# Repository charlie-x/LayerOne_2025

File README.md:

# LayerOne 2025 GLiTCh BadgE

later on there are ai generated docs...

altium link.. there is an eror on one of the leds on the charlieplex'd leds...
also the 3 pin JST SWD is reversed
.
https://365.altium.com/files/01BF9671-6FB8-4A9E-9FD1-49A52BA8D165

first flash drive appears as RPI-RP2 copy the uf2 file to it, after that use the system command to reboot to the dfu or hold the RP-BOOT button during power on or a reset cycle

the pico-ice can be used to test the  fpga.

https://a360.co/4dxIxcs
terminal is CR, so do cr/lf conversion.

for 3v3 control the pads need to be soldered on the pcb,

switch_pwr  
short 1-2

glitch_ctrl
solder all three
short 1-2-3

3cv3_ctrl
short 1-2-3

fet
short 1-2-3

https://a360.co/4dxIxcs

thea re two pots vr1, vr2 , vr1 changes run votlage of vtg, vr2 controls the low voltage

diag scripts will find

Serial Ports for CMSIS-DAP
==========================

Found serial ports:
crw-rw-rw-  1 root  wheel  0x9000003 May 25 08:40 /dev/cu.usbmodem1202

first serial port is the CDC
crw-rw-rw-  1 root  wheel  0x9000005 May 25 08:40 /dev/cu.usbmodem14301

is for hook up to the fpga etc
crw-rw-rw-  1 root  wheel  0x9000009 May 25 08:40 /dev/cu.usbmodem14303

adc streaming , two adc's interlevaed see the adc python script

crw-rw-rw-  1 root  wheel  0x9000007 May 25 08:40 /dev/cu.usbmodem14305

the adc streaming is seperate and always runs

// run it
python adc_stream_reader.py /dev/cu.usbmodem14305

// pack ADC values into buffer
 - #define HEADER_BYTE 0xAA
 - #define PACKET_SIZE 5
 - 
 - void pack_adc_values(uint16_t _adc0, uint16_t _adc1, uint8_t seq, uint8_t* buffer) {
 -    buffer[0] = HEADER_BYTE;                      // header byte for synchronization
 -    buffer[1] = seq;                              // sequence number
 -     buffer[2] = _adc0 & 0xFF;                      // low 8 bits of adc0
 -     buffer[3] = ((_adc0 >> 8) & 0x0F) |            // high 4 bits of adc0
 -                 ((_adc1 & 0x0F) << 4);             // low 4 bits of adc1
 -     buffer[4] = (_adc1 >> 4) & 0xFF;               // high 8 bits of adc1
 - }

tats for LayerOne2025 codebase:

  Files by type:
  - C (.c): 57 files
  - Headers (.h): 48 files
  - Python (.py): 25 files
  - Markdown (.md): 17 files
  - Shell scripts (.sh): 8 files

  Code metrics:
  - Total lines of code: ~30,383 lines
  - Total commits: 82
  - Contributors: 2 (charliex: 82)

  Top directories:
  - Root directory (372 files)
  - cli/ (42 files)
  - docs/ (12 files)

## Overview

The LayerOne 2025 GLiTCh BadgE is a versatile hardware hacking platform designed for security researchers, hardware enthusiasts, and anyone interested in exploring digital electronics. It combines a powerful RP2040 microcontroller with specialized hardware for glitching, debugging, and interfacing with other devices.

## Features

- **RP2040 Microcontroller** - Dual-core ARM Cortex-M0+ processor
- **ICE40 FPGA** - Programmable logic for custom hardware implementations
- **Voltage Glitcher** - For performing precise voltage glitching attacks
- **Crowbar Circuit** - For power line manipulation
- **SWD Interface** - For debugging ARM-based targets
- **AVRISP** - For programming AVR microcontrollers
- **Analog Monitoring** - For capturing and analyzing signals
- **Multiple USB Modes** - Normal, DAP, and DFU modes for different use cases
- **Basic Logic Analyser** - Simple 12 bit LA at about 10khz
  
## Documentation

Comprehensive documentation is available in the [docs](docs/) directory:

- [Quick Start Guide](docs/quick_start.md) - Get up and running with your badge
- [CLI User Guide](docs/cli_user_guide.md) - Learn how to use the Command Line Interface
- [USB Modes Guide](docs/usb_modes_guide.md) - Understand the different USB modes
- [Hardware Hacking Guide](docs/hardware_hacking_guide.md) - Explore the hardware hacking features
- [Glitching Techniques Guide](docs/glitching_techniques.md) - Detailed guide on voltage, reset, and crowbar glitching
- [ADC Signal Analysis Guide](docs/adc_signal_analysis.md) - How to use the ADC for signal capture and analysis
- [AVRISP Programming Guide](docs/avrisp_programming_guide.md) - Program AVR microcontrollers with the badge
- [Documenting Research](docs/documenting_research.md) - Best practices for documenting hardware security research
- [Command Reference](docs/command_reference.md) - Quick reference for all CLI commands
- [Case Studies](docs/case_studies/README.md) - Real-world examples of hardware security vulnerabilities
  - [nRF52 Glitch Attack](docs/case_studies/nrf52_glitch_attack.md) - Voltage glitching attack on Nordic's BLE SoC

## Getting Started

### Prerequisites

- Python 3.6 or higher
- PySerial library (`pip install pyserial`)
- PyOCD for debugging (`pip install pyocd`)

### Installation

1. Clone this repository:
   ```
   git clone git@github.com:charlie-x/LayerOne_2025.git
   cd LayerOne_2025
   ```

2. Connect your badge to your computer using a USB-C cable
   Either use the RP-BOOT switch to put the badge into RPI-RP2 mode while its in reset, or switch on. or if its already flashed you can use system dfu command on the badge itself, copy the uf2/layerOne2025.uf2 file to the RPI-RP2 folder, use -X if you use cp in Mac OS
  
4. Run the CLI terminal:
   ```
   python3 cli_terminal.py
   ```

### Basic Usage

Once connected to the CLI, you can use commands like:

```
help            # Show available commands
status          # Show badge status
rgb on          # Turn on the RGB LED
usb mode dap    # Switch to DAP mode
```

For a complete list of commands, see the [Command Reference](docs/command_reference.md).

## USB Modes

The badge supports three USB modes:

1. **Normal Mode** (default) - 3 CDC interfaces + Mass Storage
2. **DAP Mode** - CMSIS-DAP debugging interface + CDC
3. **DFU Mode** - Device Firmware Update mode

To switch between modes, use the `usb mode` command:

```
usb mode normal     # Switch to normal mode
usb mode dap        # Switch to DAP mode
usb mode dfu        # Switch to DFU mode
```

## Logic Analyser mode

use command 

adc_stream la

## Development

### Building the Firmware

To build the firmware:

```
./build.sh
```

### Flashing the Firmware

To build and flash the firmware:

```
./build_and_flash.sh
```

### Running Tests

To run the USB mode tests:

```
python3 test_usb_modes.py
```

## Contributing

We welcome contributions to improve the badge and its documentation! Please see the [Contributing Guide](docs/contributing.md) for details on how to contribute.

## License

The LayerOne 2025 GLiTCh BadgE firmware and hardware designs are licensed under [MIT License](https://opensource.org/licenses/MIT).

## Acknowledgments

The LayerOne 2025 GLiTCh BadgE was created by NullSpaceLabs for the LayerOne 2025 conference. Special thanks to all the contributors and the hardware hacking community for their support and inspiration.

## Contact

- Website: [nullspacelabs.com](https://nullspacelabs.com)
- Email: [info@nullspacelabs.com](mailto:info@nullspacelabs.com)
- Twitter: [@nullspacelabs](https://twitter.com/nullspacelabs)

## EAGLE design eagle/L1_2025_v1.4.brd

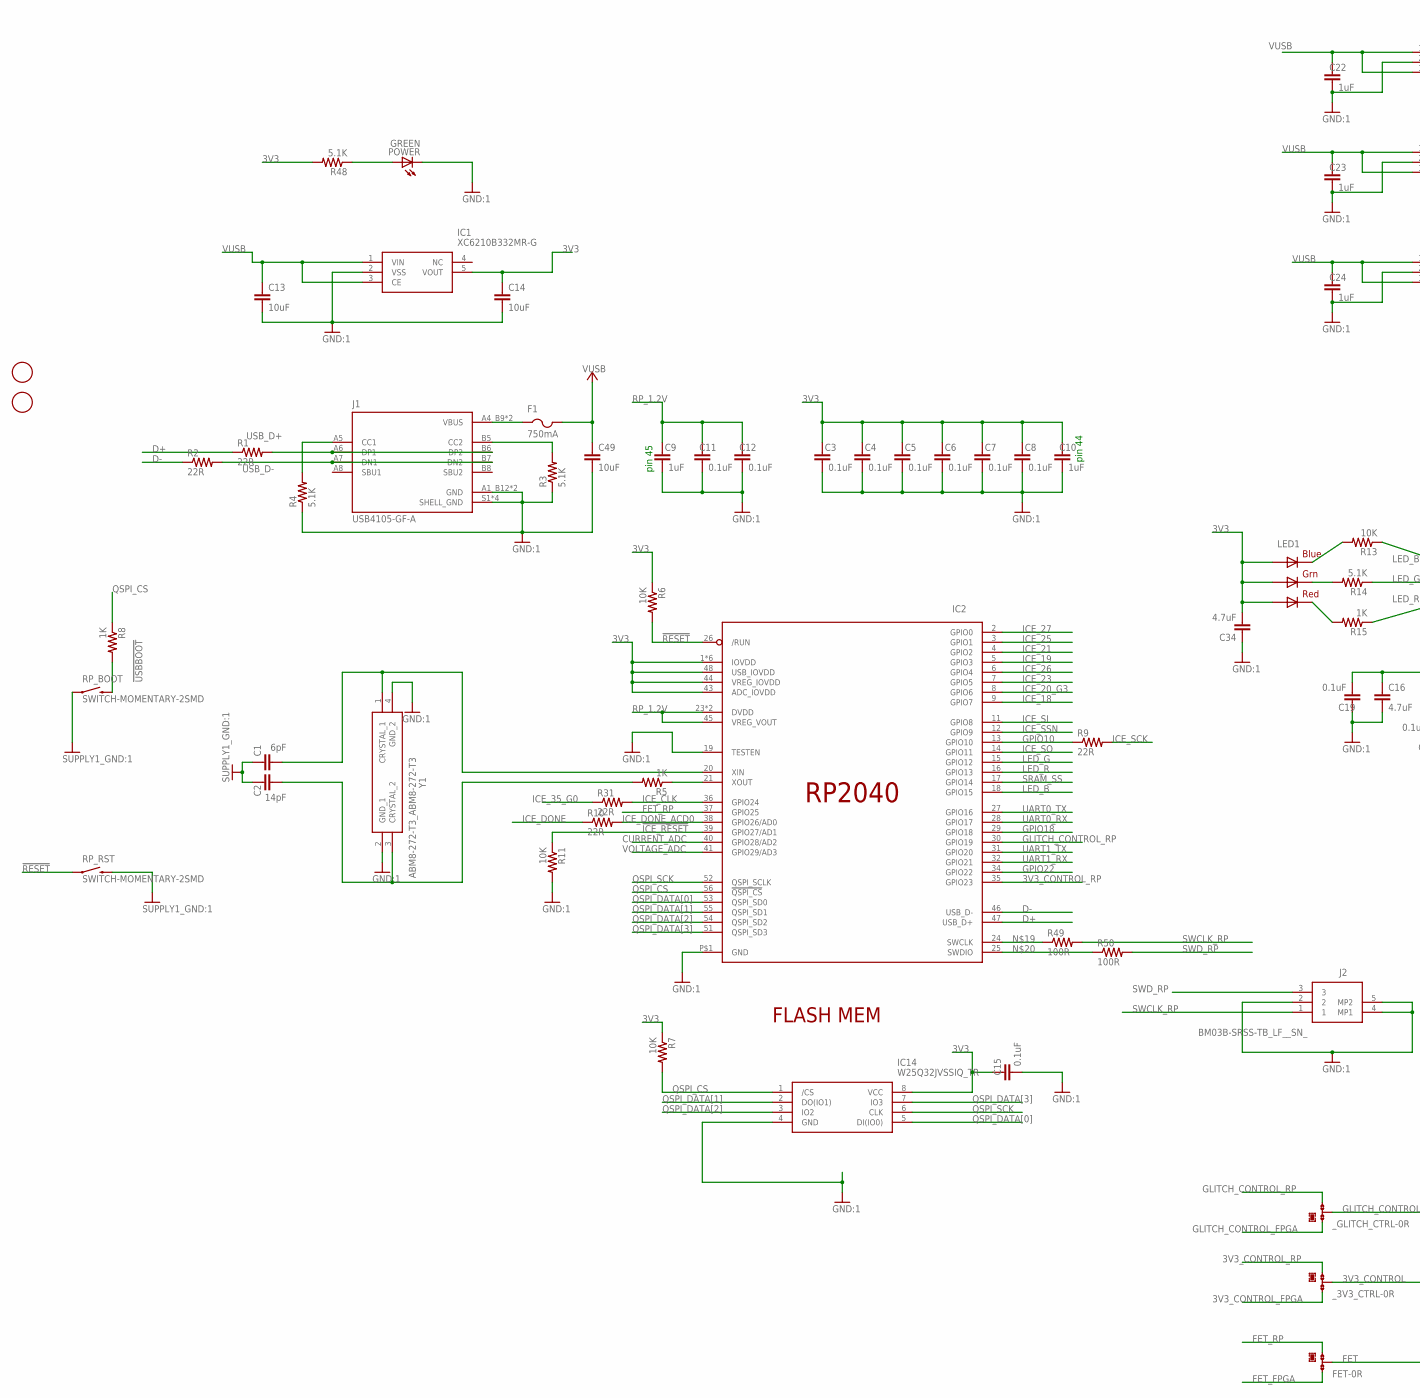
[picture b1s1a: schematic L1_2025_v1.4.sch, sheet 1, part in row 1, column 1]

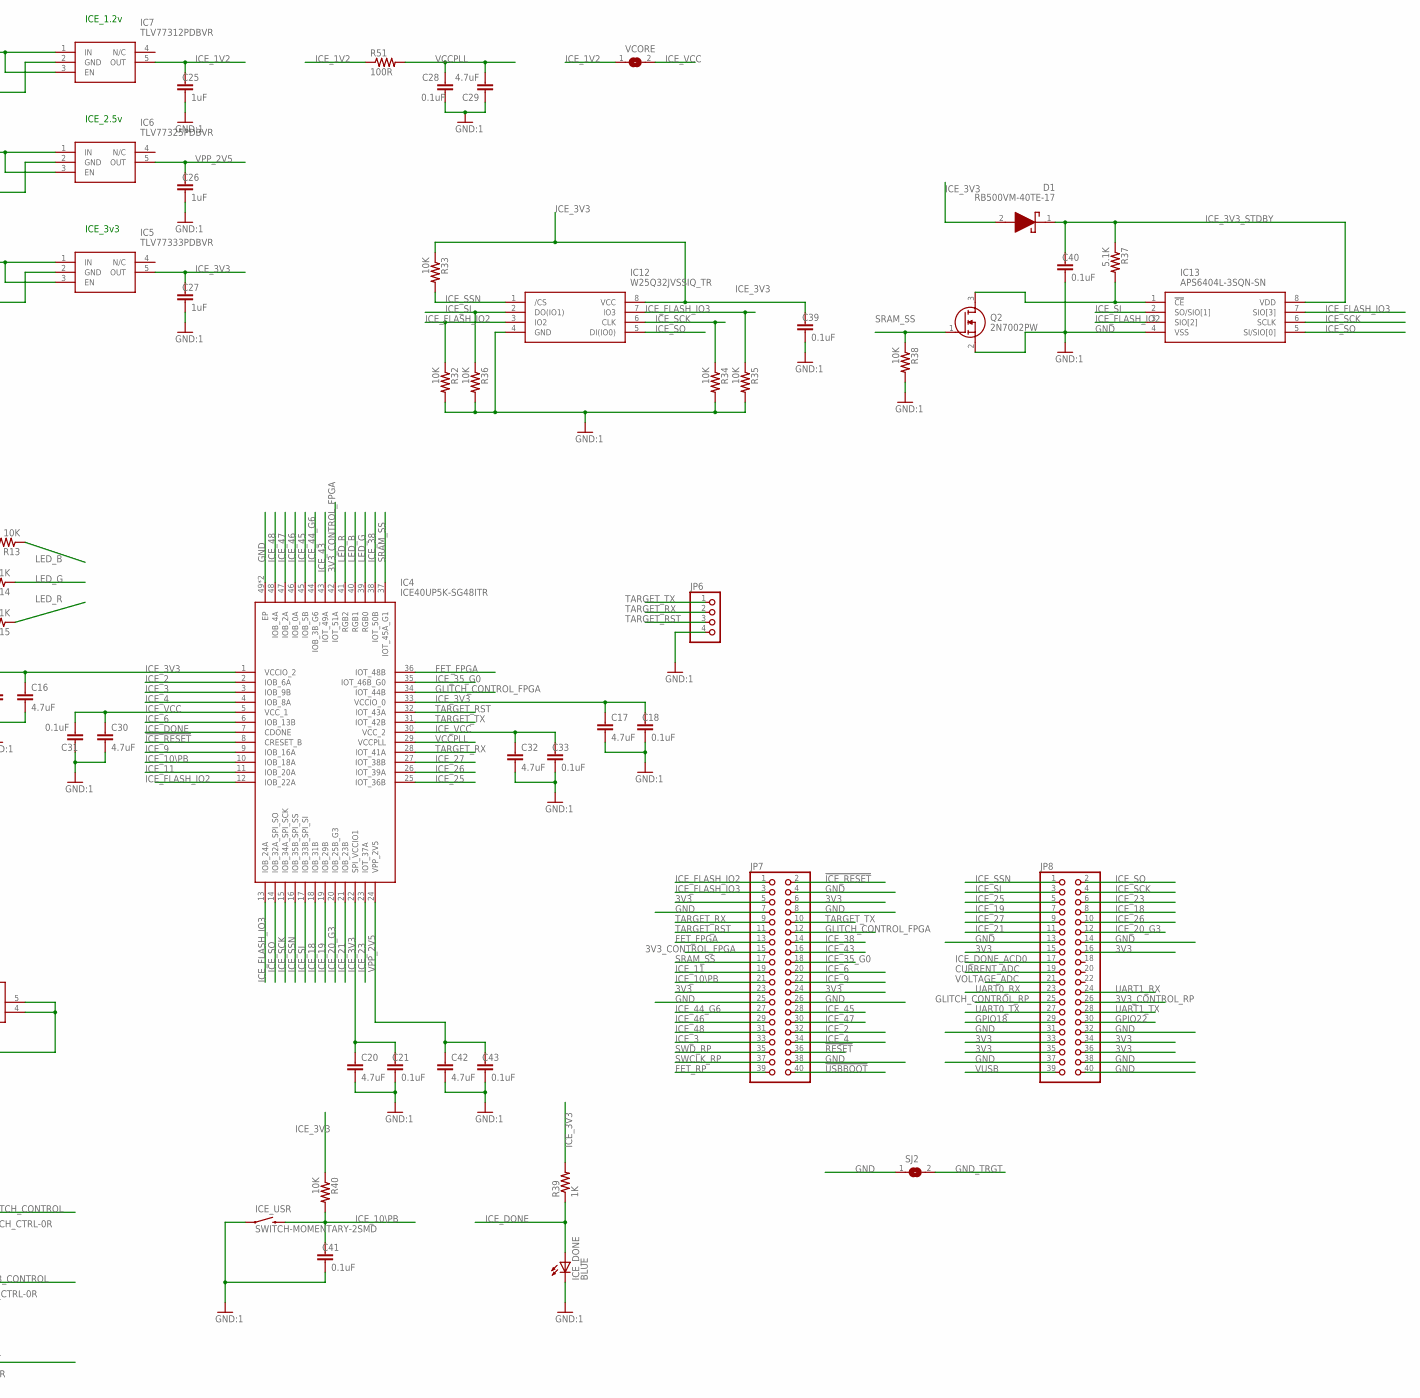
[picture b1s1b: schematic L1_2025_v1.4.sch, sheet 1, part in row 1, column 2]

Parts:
AFID1, AFID2: FIDUCIAL; FIDUCIAL_1MM
C1: 6pF; 0402-CAP
C2: 14pF; 0402-CAP
C3, C4, C5, C6, C7, C8, C11, C12, C15, C18, C19, C21, C28, C31, C33, C39, C40, C41, C43: 0.1uF; 0402-CAP
C9, C10, C22, C23, C24, C25, C26, C27: 1uF; 0402-CAP
C13, C14, C49: 10uF; 0603-CAP
C16, C17, C20, C29, C30, C32, C34, C42: 4.7uF; 0603-CAP
D1: RB500VM-40TE-17; RB500VM40TE17
F1: 750mA; R1206
FET: 0R-JUMPC; C0R-JMP
IC1: XC6210B332MR-G; SOT95P280X130-5N
IC2: ADAFRUIT_MICRO_RP2040_QFN56; ADAFRUIT_MICRO_QFN56_7MM_REDUCEDEPAD
IC4: ICE40UP5K-SG48ITR; QFN50P700X700X100-49N
IC5: TLV77333PDBVR; SOT95P280X145-5N
IC6: TLV77325PDBVR; SOT95P280X145-5N
IC7: TLV77312PDBVR; SOT95P280X145-5N
IC12, IC14: W25Q32JVSSIQ_TR; SOIC127P790X216-8N
IC13: APS6404L-3SQN-SN; SOIC127P600X175-8N
ICE_DONE: BLUE; LED-1206
ICE_USR: SWITCH-MOMENTARY-2SMD; TACTILE_SWITCH_SMD
J1: USB4105-GF-A; GCT_USB4105-GF-A
J2: BM03B-SRSS-TB_LF__SN_; BM03BSRSSTBLFSN
JP6: PINHD-1X4; 1X04
JP7, JP8: PINHD-2X20-BIG; 2X20-BIG
LED1: RGBLED5050
POWER: GREEN; LED-1206
Q2: 2N7002PW; SOT65P210X110-3N
R1, R2, R9, R10, R31: 22R; 0402-RES:1
R3, R4, R14, R37, R48: 5.1K; 0402-RES:1
R5, R8, R15, R39: 1K; 0402-RES:1
R6, R7, R11, R13, R32, R33, R34, R35, R36, R38, R40: 10K; 0402-RES:1
R49, R50, R51: 100R; 0402-RES:1
RP_BOOT: SWITCH-MOMENTARY-2SMD; TACTILE_SWITCH_SMD
RP_RST: SWITCH-MOMENTARY-2SMD; TACTILE_SWITCH_SMD
SJ2: SJ
VCORE: SJ
Y1: ABM8-272-T3_ABM8-272-T3; ABM8-272-T3_ABM8272T3
_3V3_CTRL: 0R-JUMPC; C0R-JMP
_GLITCH_CTRL: 0R-JUMPC; C0R-JMP

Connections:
3V3: C3.2, C4.2, C5.2, C6.2, C7.2, C8.2, C10.2, C14.1, C15.2, C34.2, IC1.5 (VOUT), IC2.1 (IOVDD), IC2.10 (IOVDD), IC2.22 (IOVDD), IC2.33 (IOVDD), IC2.42 (IOVDD), IC2.43 (ADC_IOVDD), IC2.44 (VREG_IOVDD), IC2.48 (USB_IOVDD), IC2.49 (IOVDD), IC14.8 (VCC), JP7.5, JP7.6, JP7.23, JP7.24, JP8.15, JP8.16, JP8.33, JP8.34, JP8.35, JP8.36, LED1.1 (GREEN_A), LED1.2 (RED_A), LED1.3 (BLUE_A), R6.1, R7.1, R48.2; also elsewhere on the board
3V3_CONTROL: _3V3_CTRL.2; also elsewhere on the board
3V3_CONTROL_FPGA: IC4.42 (IOT_51A), JP7.15, _3V3_CTRL.3
3V3_CONTROL_RP: IC2.35 (GPIO23), JP8.26, _3V3_CTRL.1
!ICE_RESET: IC2.39 (GPIO27/AD1), IC4.8 (CRESET_B), JP7.2, R11.1
!RESET: IC2.26 (/RUN), JP7.36, R6.2, RP_RST.1
!USBBOOT: JP7.40, R8.2, RP_BOOT.3 (2)
CURRENT_ADC: IC2.40 (GPIO28/AD2), JP8.19; also elsewhere on the board
D+: IC2.47 (USB_D+), R1.1
D-: IC2.46 (USB_D-), R2.1
FET: FET.2; also elsewhere on the board
FET_FPGA: FET.3, IC4.36 (IOT_48B), JP7.13
FET_RP: FET.1, IC2.37 (GPIO25), JP7.39
GLITCH_CONTROL: _GLITCH_CTRL.2; also elsewhere on the board
GLITCH_CONTROL_FPGA: IC4.34 (IOT_44B), JP7.12, _GLITCH_CTRL.3
GLITCH_CONTROL_RP: IC2.30 (GPIO19), JP8.25, _GLITCH_CTRL.1
GND: C1.1, C2.1, C3.1, C4.1, C5.1, C6.1, C7.1, C8.1, C9.1, C10.1, C11.1, C12.1, C13.2, C14.2, C15.1, C16.2, C17.2, C18.1, C19.2, C20.2, C21.1, C22.1, C23.1, C24.1, C25.1, C26.1, C27.1, C28.1, C29.1, C30.2, C31.2, C32.2, C33.1, C34.1, C39.1, C40.1, C41.1, C42.2, C43.1, C49.2, IC1.2 (VSS), IC2.19 (TESTEN), IC2.P$1 (GND), IC4.49 (EP), IC4.P$1 (EP), IC5.2 (GND), IC6.2 (GND), IC7.2 (GND), IC12.4 (GND), IC13.4 (VSS), IC14.4 (GND), ICE_DONE.C, ICE_USR.1, J1.A1_B12 (GND), J1.B1_A12 (GND), J1.S1 (SHELL_GND), J1.S2 (SHELL_GND), J1.S3 (SHELL_GND), J1.S4 (SHELL_GND), J2.2, J2.4 (MP1), J2.5 (MP2), JP6.4, JP7.4, JP7.7, JP7.8, JP7.25, JP7.26, JP7.38, JP8.13, JP8.14, JP8.31, JP8.32, JP8.37, JP8.38, JP8.40, POWER.C, Q2.2 (S), R3.1, R4.1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; also elsewhere on the board
GND_TRGT: SJ2.2; also elsewhere on the board
GPIO10: IC2.13 (GPIO10), R9.1
GPIO18: IC2.29 (GPIO18), JP8.29; also elsewhere on the board
GPIO22: IC2.34 (GPIO22), JP8.30; also elsewhere on the board
ICE_1V2: C25.2, IC7.5 (OUT), R51.1, VCORE.1
ICE_2: IC4.2 (IOB_6A), JP7.32
ICE_3: IC4.3 (IOB_9B), JP7.33
ICE_3V3: C16.1, C17.1, C18.2, C19.1, C20.1, C21.2, C27.2, C39.2, D1.2 (A), IC4.1 (VCCIO_2), IC4.22 (SPI_VCCIO1), IC4.33 (VCCIO_0), IC5.5 (OUT), IC12.8 (VCC), R33.1, R39.2, R40.1
ICE_3V3_STDBY: C40.2, D1.1 (K), IC13.8 (VDD), R37.1
ICE_4: IC4.4 (IOB_8A), JP7.34
ICE_6: IC4.6 (IOB_13B), JP7.20
ICE_9: IC4.9 (IOB_16A), JP7.22
ICE_10\PB: C41.2, IC4.10 (IOB_18A), ICE_USR.3 (2), JP7.21, R40.2
ICE_11: IC4.11 (IOB_20A), JP7.19
ICE_18: IC2.9 (GPIO7), IC4.18 (IOB_31B), JP8.8
ICE_19: IC2.5 (GPIO3), IC4.19 (IOB_29B), JP8.7
ICE_20_G3: IC2.8 (GPIO6), IC4.20 (IOB_25B_G3), JP8.12
ICE_21: IC2.4 (GPIO2), IC4.21 (IOB_23B), JP8.11
ICE_23: IC2.7 (GPIO5), IC4.23 (IOT_37A), JP8.6
ICE_25: IC2.3 (GPIO1), IC4.25 (IOT_36B), JP8.5
ICE_26: IC2.6 (GPIO4), IC4.26 (IOT_39A), JP8.10
ICE_27: IC2.2 (GPIO0), IC4.27 (IOT_38B), JP8.9
ICE_35_G0: IC4.35 (IOT_46B_G0), JP7.18, R31.1
ICE_38: IC4.38 (IOT_50B), JP7.14
ICE_43: IC4.43 (IOT_49A), JP7.16
ICE_44_G6: IC4.44 (IOB_3B_G6), JP7.27
ICE_45: IC4.45 (IOB_5B), JP7.28
ICE_46: IC4.46 (IOB_0A), JP7.29
ICE_47: IC4.47 (IOB_2A), JP7.30
ICE_48: IC4.48 (IOB_4A), JP7.31
ICE_CLK: IC2.36 (GPIO24), R31.2
ICE_DONE: IC4.7 (CDONE), ICE_DONE.A, R10.1, R39.1
ICE_DONE_ACD0: IC2.38 (GPIO26/AD0), JP8.17, R10.2
ICE_FLASH_IO2: IC4.12 (IOB_22A), IC12.3 (IO2), IC13.3 (SIO[2]), JP7.1, R32.1
ICE_FLASH_IO3: IC4.13 (IOB_24A), IC12.7 (IO3), IC13.7 (SIO[3]), JP7.3, R35.1
ICE_SCK: IC4.15 (IOB_34A_SPI_SCK), IC12.6 (CLK), IC13.6 (SCLK), JP8.4, R9.2, R34.1
ICE_SI: IC2.11 (GPIO8), IC4.17 (IOB_33B_SPI_SI), IC12.2 (DO(IO1)), IC13.2 (SO/SIO[1]), JP8.3, R36.1
ICE_SO: IC2.14 (GPIO11), IC4.14 (IOB_32A_SPI_SO), IC12.5 (DI(IO0)), IC13.5 (SI/SIO[0]), JP8.2
ICE_SSN: IC2.12 (GPIO9), IC4.16 (IOB_35B_SPI_SS), IC12.1 (/CS), JP8.1, R33.2
ICE_VCC: C30.1, C31.1, C32.1, C33.2, IC4.5 (VCC_1), IC4.30 (VCC_2), VCORE.2
LED_B: IC2.18 (GPIO15), IC4.40 (RGB1), R13.1
LED_G: IC2.15 (GPIO12), IC4.39 (RGB0), R14.1
LED_R: IC2.16 (GPIO13), IC4.41 (RGB2), R15.1
unnamed: C2.2, R5.2, Y1.3 (CRYSTAL_2)
unnamed: IC2.21 (XOUT), R5.1
unnamed: C1.2, IC2.20 (XIN), Y1.1 (CRYSTAL_1)
unnamed: LED1.4 (BLUE_C), R13.2
unnamed: LED1.6 (GREEN_C), R14.2
unnamed: LED1.5 (RED_C), R15.2
unnamed: J1.A5 (CC1), R4.2
unnamed: J1.B5 (CC2), R3.2
unnamed: IC13.1 (!CE), Q2.3 (D), R37.2
unnamed: F1.1, J1.A4_B9 (VBUS), J1.B4_A9 (VBUS)
unnamed: POWER.A, R48.1
unnamed: IC2.24 (SWCLK), R49.1
unnamed: IC2.25 (SWDIO), R50.1
QSPI_CS: IC2.56 (!QSPI_CS), IC14.1 (/CS), R7.2, R8.1
QSPI_DATA[0]: IC2.53 (QSPI_SD0), IC14.5 (DI(IO0))
QSPI_DATA[1]: IC2.55 (QSPI_SD1), IC14.2 (DO(IO1))
QSPI_DATA[2]: IC2.54 (QSPI_SD2), IC14.3 (IO2)
QSPI_DATA[3]: IC2.51 (QSPI_SD3), IC14.7 (IO3)
QSPI_SCK: IC2.52 (QSPI_SCLK), IC14.6 (CLK)
RP_1.2V: C9.2, C11.2, C12.2, IC2.23 (DVDD), IC2.45 (VREG_VOUT), IC2.50 (DVDD)
SRAM_SS: IC2.17 (GPIO14), IC4.37 (IOT_45A_G1), JP7.17, Q2.1 (G), R38.1
SWCLK_RP: J2.1, JP7.37, R49.2
SWD_RP: J2.3, JP7.35, R50.2
TARGET_RST: IC4.32 (IOT_43A), JP6.3, JP7.11
TARGET_RX: IC4.28 (IOT_41A), JP6.2, JP7.9
TARGET_TX: IC4.31 (IOT_42B), JP6.1, JP7.10
UART0_RX: IC2.28 (GPIO17), JP8.23; also elsewhere on the board
UART0_TX: IC2.27 (GPIO16), JP8.27; also elsewhere on the board
UART1_RX: IC2.32 (GPIO21), JP8.24; also elsewhere on the board
UART1_TX: IC2.31 (GPIO20), JP8.28; also elsewhere on the board
USB_D+: J1.A6 (DP1), J1.B6 (DP2), R1.2
USB_D-: J1.A7 (DN1), J1.B7 (DN2), R2.2
VCCPLL: C28.2, C29.2, IC4.29 (VCCPLL), R51.2
VOLTAGE_ADC: IC2.41 (GPIO29/AD3), JP8.21; also elsewhere on the board
VPP_2V5: C26.2, C42.1, C43.2, IC4.24 (VPP_2V5), IC6.5 (OUT)
VUSB: C13.1, C22.2, C23.2, C24.2, C49.1, F1.2, IC1.1 (VIN), IC1.3 (CE), IC5.1 (IN), IC5.3 (EN), IC6.1 (IN), IC6.3 (EN), IC7.1 (IN), IC7.3 (EN), JP8.39; also elsewhere on the board

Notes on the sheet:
pin 45
pin 44
FLASH MEM
ICE_3v3
ICE_2.5v
ICE_1.2v

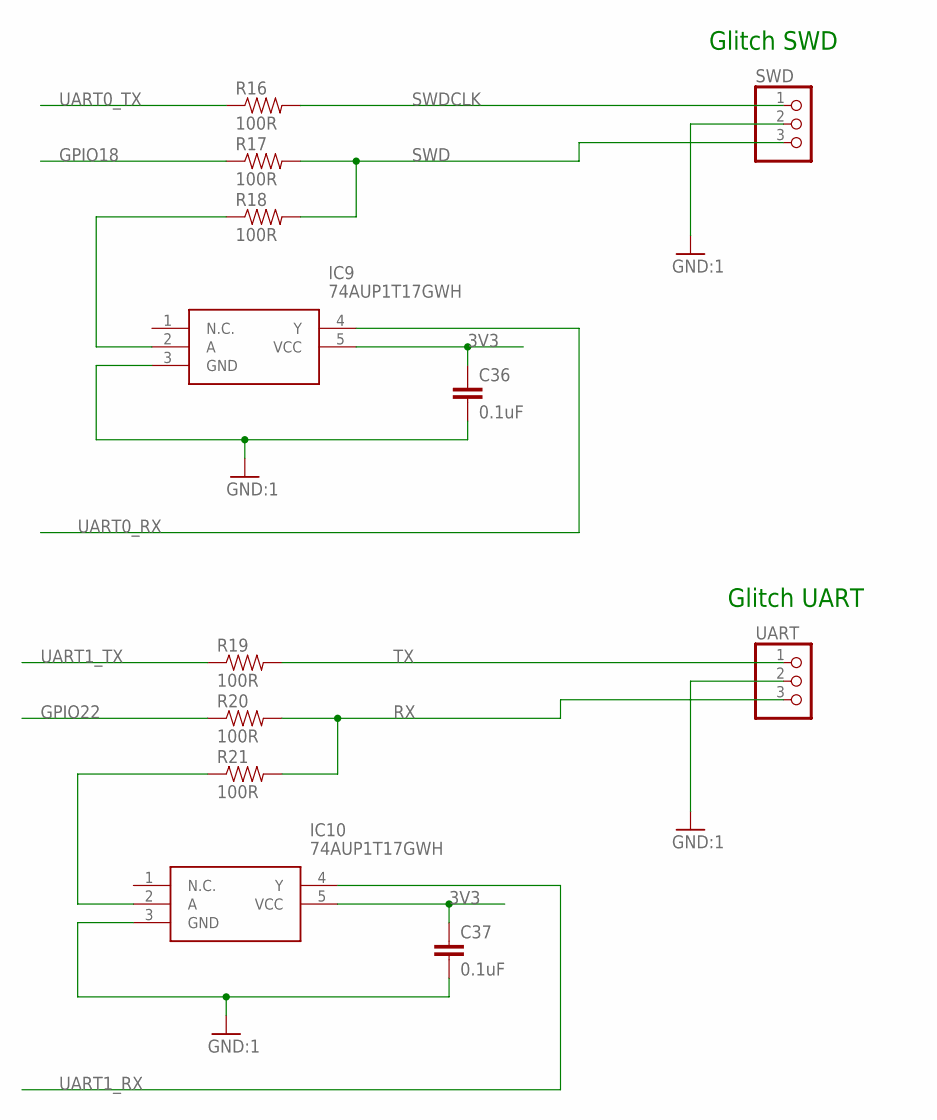
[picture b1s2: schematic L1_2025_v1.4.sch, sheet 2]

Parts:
C36, C37: 0.1uF; 0402-CAP
IC9, IC10: 74AUP1T17GWH; SOT65P212X110-5N
R16, R17, R18, R19, R20, R21: 100R; 0402-RES:1
SWD: PINHD-1X3; 1X03
UART: PINHD-1X3; 1X03

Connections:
3V3: C36.1, C37.1, IC9.5 (VCC), IC10.5 (VCC); also elsewhere on the board
GND: C36.2, C37.2, IC9.3 (GND), IC10.3 (GND), SWD.2, UART.2; also elsewhere on the board
GPIO18: R17.1; also elsewhere on the board
GPIO22: R20.1; also elsewhere on the board
unnamed: IC10.2 (A), R21.1
unnamed: IC9.2 (A), R18.1
RX: R20.2, R21.2, UART.3
SWD: R17.2, R18.2, SWD.3
SWDCLK: R16.2, SWD.1
TX: R19.2, UART.1
UART0_RX: IC9.4 (Y); also elsewhere on the board
UART0_TX: R16.1; also elsewhere on the board
UART1_RX: IC10.4 (Y); also elsewhere on the board
UART1_TX: R19.1; also elsewhere on the board

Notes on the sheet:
Glitch SWD
Glitch UART

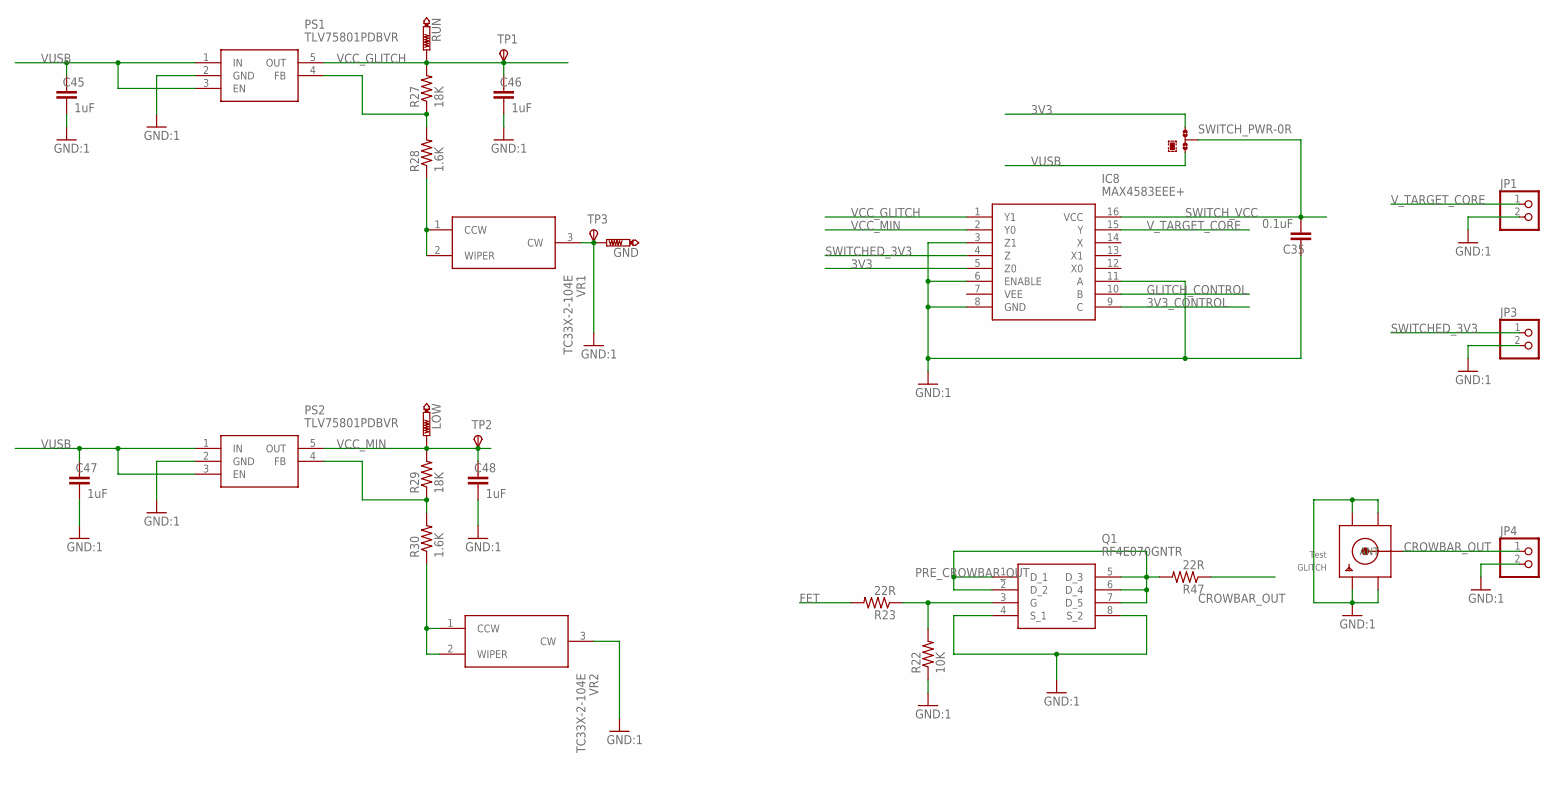
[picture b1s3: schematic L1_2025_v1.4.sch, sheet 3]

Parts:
C35: 0.1uF; 0402-CAP
C45, C46, C47, C48: 1uF; 0402-CAP
GLITCH: Test; SMA_EDGELAUNCH
GND: PTR1PAD1-13; P1-13
IC8: MAX4583EEE+; SOP64P602X175-16N
JP1, JP3, JP4: PINHD-1X2; 1X02
LOW: PTR1PAD1-13; P1-13
PS1, PS2: TLV75801PDBVR; SOT95P280X145-5N
Q1: RF4E070GNTR
R22: 10K; 0402-RES:1
R23, R47: 22R; 0402-RES:1
R27, R29: 18K; 0402-RES:1
R28, R30: 1.6K; 0402-RES:1
RUN: PTR1PAD1-13; P1-13
SWITCH_PWR: 0R-JUMPC; C0R-JMP
TP1, TP2, TP3: TESTPAD_TPSTP20R; TESTPAD_TP20R:1
VR1, VR2: TC33X-2-104E; TC33X2503E

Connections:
3V3: IC8.5 (Z0), SWITCH_PWR.1; also elsewhere on the board
3V3_CONTROL: IC8.9 (C); also elsewhere on the board
CROWBAR_OUT: GLITCH.P (ANT), JP4.1, R47.1
FET: R23.2; also elsewhere on the board
GLITCH_CONTROL: IC8.10 (B); also elsewhere on the board
GND: C35.2, C45.1, C46.1, C47.1, C48.1, GLITCH.GND@1 (GND4), GLITCH.GND@2 (GND3), GLITCH.GND@3 (GND2), GLITCH.GND@4 (GND1), GND.TP, IC8.3 (Z1), IC8.6 (ENABLE), IC8.8 (GND), IC8.11 (A), JP1.2, JP3.2, JP4.2, PS1.2 (GND), PS2.2 (GND), Q1.4 (S_1), Q1.8 (S_2), R22.1, TP3.TP, VR1.3 (CW), VR2.3 (CW); also elsewhere on the board
unnamed: PS1.4 (FB), R27.1, R28.2
unnamed: Q1.3 (G), R22.2, R23.1
unnamed: R28.1, VR1.1 (CCW), VR1.2 (WIPER)
unnamed: PS2.4 (FB), R29.1, R30.2
unnamed: R30.1, VR2.1 (CCW), VR2.2 (WIPER)
PRE_CROWBAR_OUT: Q1.1 (D_1), Q1.2 (D_2), Q1.5 (D_3), Q1.6 (D_4), Q1.7 (D_5), R47.2
SWITCHED_3V3: IC8.4 (Z), JP3.1
SWITCH_VCC: C35.1, IC8.16 (VCC), SWITCH_PWR.2
VCC_GLITCH: C46.2, IC8.1 (Y1), PS1.5 (OUT), R27.2, RUN.TP, TP1.TP
VCC_MIN: C48.2, IC8.2 (Y0), LOW.TP, PS2.5 (OUT), R29.2, TP2.TP
VUSB: C45.2, C47.2, PS1.1 (IN), PS1.3 (EN), PS2.1 (IN), PS2.3 (EN), SWITCH_PWR.3; also elsewhere on the board
V_TARGET_CORE: IC8.15 (Y), JP1.1

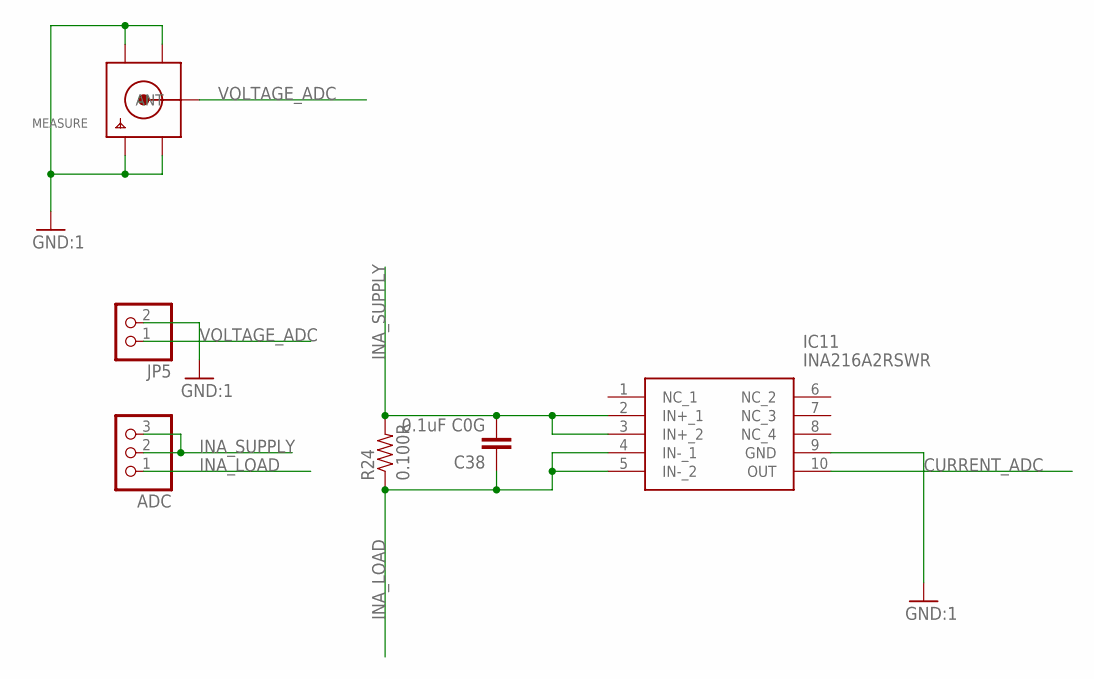
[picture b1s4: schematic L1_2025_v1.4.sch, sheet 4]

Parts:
ADC: PINHD-1X3:1; 1X03:1
C38: 0.1uF C0G; 0402-CAP
IC11: INA216A2RSWR
JP5: PINHD-1X2; 1X02
MEASURE: SMACONNECTOR_EDGE; SMA_EDGELAUNCH
R24: 0.100R; R2512

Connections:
CURRENT_ADC: IC11.10 (OUT); also elsewhere on the board
GND: IC11.9 (GND), JP5.2, MEASURE.GND@1 (GND4), MEASURE.GND@2 (GND3), MEASURE.GND@3 (GND2), MEASURE.GND@4 (GND1); also elsewhere on the board
INA_LOAD: ADC.1, C38.1, IC11.4 (IN-_1), IC11.5 (IN-_2), R24.1
INA_SUPPLY: ADC.2, ADC.3, C38.2, IC11.2 (IN+_1), IC11.3 (IN+_2), R24.2
VOLTAGE_ADC: JP5.1, MEASURE.P (ANT); also elsewhere on the board

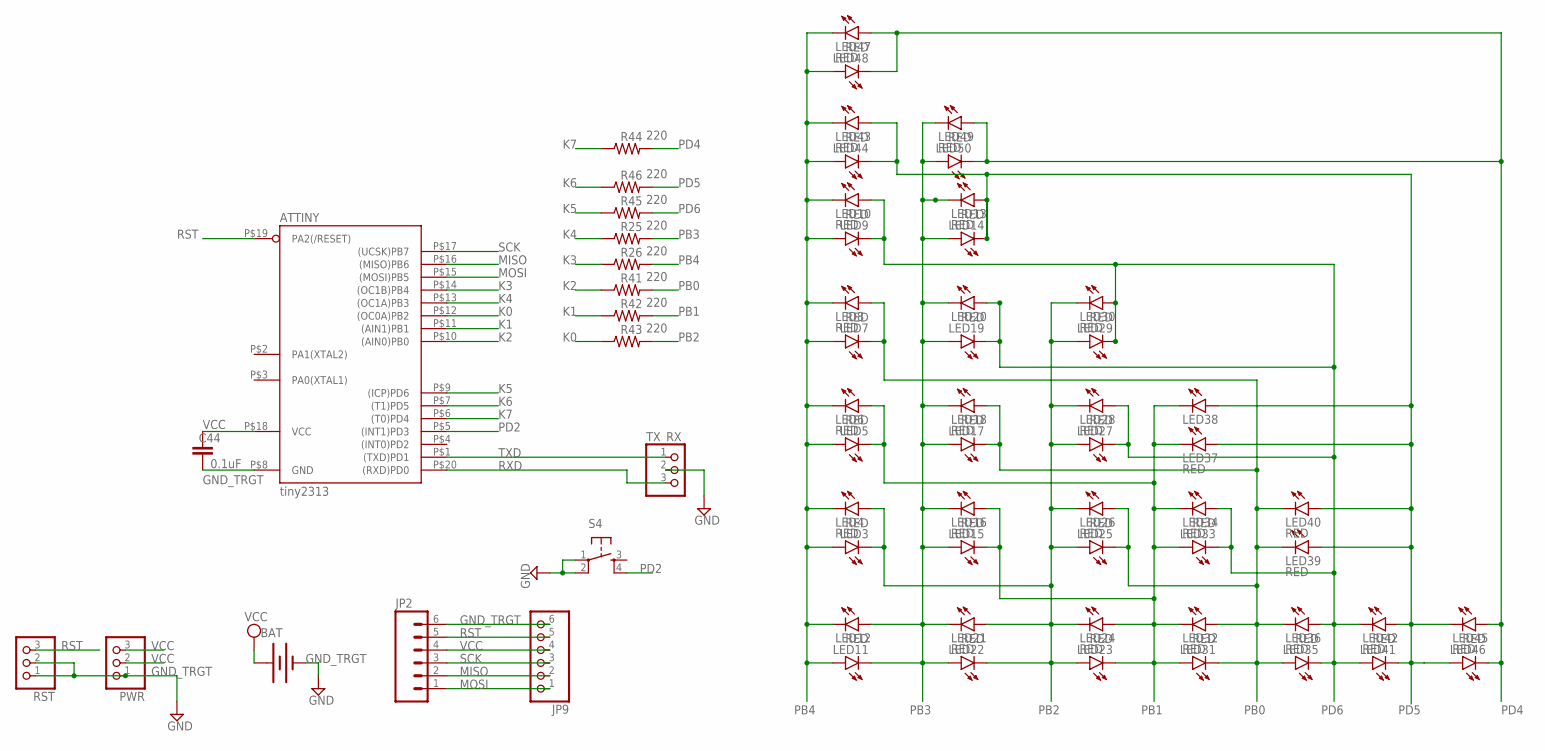
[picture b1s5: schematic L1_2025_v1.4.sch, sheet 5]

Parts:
ATTINY: tiny2313; MLF20
BAT: SPARKFUN_BATTERYSPARKFUN_BATTCOMM_20MM_LINX; SPARKFUN_BATTCOM_20MM_LINX
C44: 0.1uF; 0402-CAP
JP2: SPARKFUN-CONNECTORS_M06SMD-FEMALE-V2; SPARKFUN-CONNECTORS_1X06-SMD-FEMALE-V2
JP9: ADAFRUIT_PINHD-1X6CLEAN; ADAFRUIT_1X06-CLEAN
LED3, LED4, LED5, LED6, LED7, LED8, LED9, LED10, LED11, LED13, LED14, LED15, LED16, LED17, LED18, LED19, LED21, LED22, LED23, LED24, LED25, LED26, LED27, LED28, LED29, LED30, LED31, LED32, LED33, LED34, LED35, LED36, LED37, LED39, LED40, LED41, LED42, LED43, LED44, LED45, LED46, LED47, LED48, LED49, LED50: RED; CHIPLED_1206
LED12, LED20, LED38: LEDCHIPLED_1206:1; CHIPLED_1206
PWR: PINHD-1X3; 1X03
R25, R26, R41, R42, R43, R44, R45, R46: 220; 0805
RST: PINHD-1X3; 1X03
S4: TAC_SWITCHSMD; TACTILE_SWITCH_SMD:1
TX_RX: PINHD-1X3; 1X03

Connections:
GND_TRGT: ATTINY.P$8 (GND), BAT.2 (-), C44.1, JP2.6, JP9.6, PWR.1, RST.1, RST.2, S4.1, S4.2, TX_RX.2; also elsewhere on the board
K0: ATTINY.P$12 ((OC0A)PB2), R43.1
K1: ATTINY.P$11 ((AIN1)PB1), R42.1
K2: ATTINY.P$10 ((AIN0)PB0), R41.1
K3: ATTINY.P$14 ((OC1B)PB4), R26.1
K4: ATTINY.P$13 ((OC1A)PB3), R25.1
K5: ATTINY.P$9 ((ICP)PD6), R45.1
K6: ATTINY.P$7 ((T1)PD5), R46.1
K7: ATTINY.P$6 ((T0)PD4), R44.1
MISO: ATTINY.P$16 ((MISO)PB6), JP2.2, JP9.2
MOSI: ATTINY.P$15 ((MOSI)PB5), JP2.1, JP9.1
PB0: LED7.C, LED8.A, LED17.C, LED18.A, LED25.C, LED26.A, LED31.C, LED32.A, LED35.A, LED36.C, LED39.C, LED40.C, R41.2
PB1: LED5.C, LED6.A, LED15.C, LED16.A, LED23.C, LED24.A, LED31.A, LED32.C, LED33.A, LED34.C, LED37.C, LED38.C, R42.2
PB2: LED3.C, LED4.A, LED21.A, LED22.C, LED23.A, LED24.C, LED25.A, LED26.C, LED27.A, LED28.C, LED29.A, LED30.C, R43.2
PB3: LED11.C, LED12.A, LED13.C, LED14.A, LED15.A, LED16.C, LED17.A, LED18.C, LED19.A, LED20.C, LED21.C, LED22.A, LED49.C, LED50.A, R25.2
PB4: LED3.A, LED4.C, LED5.A, LED6.C, LED7.A, LED8.C, LED9.A, LED10.C, LED11.A, LED12.C, LED43.C, LED44.A, LED47.C, LED48.A, R26.2
PD2: ATTINY.P$5 ((INT1)PD3), S4.4
PD4: LED45.A, LED46.C, LED47.A, LED48.C, LED49.A, LED50.C, R44.2
PD5: LED13.A, LED14.C, LED37.A, LED38.A, LED39.A, LED40.A, LED41.C, LED42.A, LED43.A, LED44.C, LED45.C, LED46.A, R46.2
PD6: LED9.C, LED10.A, LED19.C, LED20.A, LED27.C, LED28.A, LED29.C, LED30.A, LED33.C, LED34.A, LED35.C, LED36.A, LED41.A, LED42.C, R45.2
RST: ATTINY.P$19 (PA2(/RESET)), JP2.5, JP9.5, RST.3
RXD: ATTINY.P$20 ((RXD)PD0), TX_RX.3
SCK: ATTINY.P$17 ((UCSK)PB7), JP2.3, JP9.3
TXD: ATTINY.P$1 ((TXD)PD1), TX_RX.1
VCC: ATTINY.P$18 (VCC), BAT.1 (+), C44.2, JP2.4, JP9.4, PWR.2, PWR.3

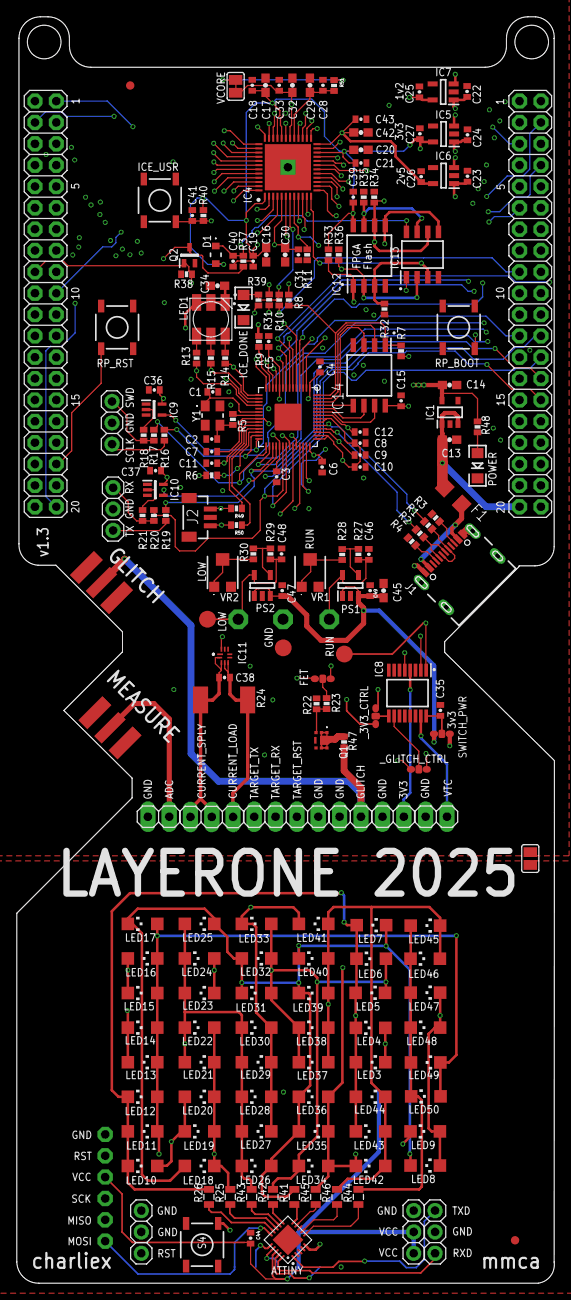
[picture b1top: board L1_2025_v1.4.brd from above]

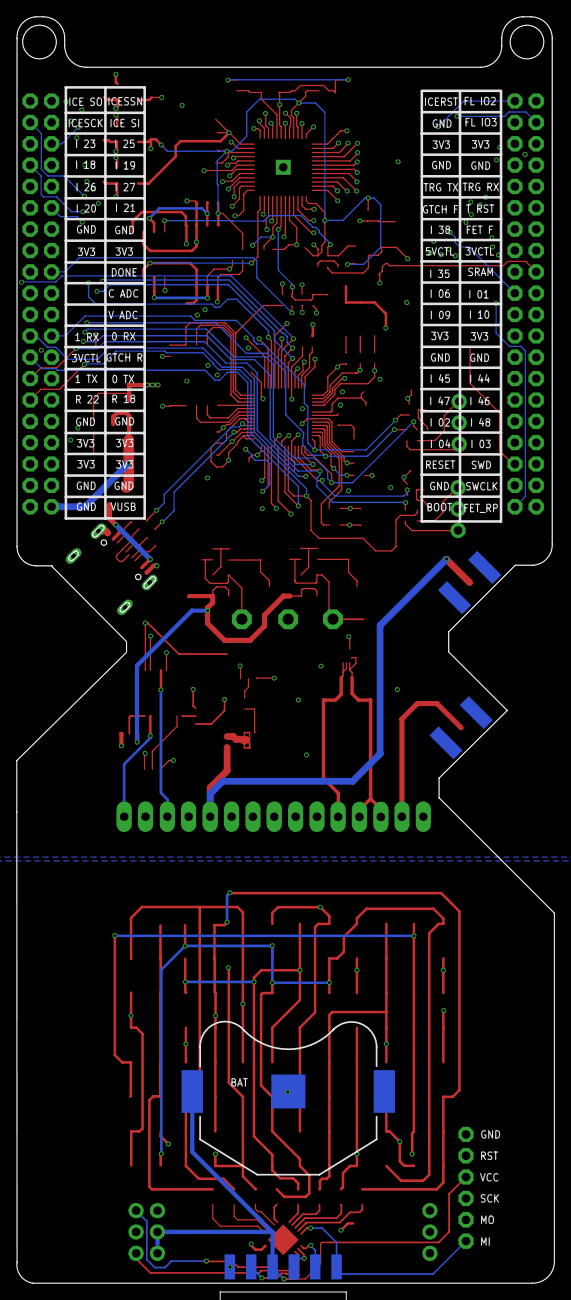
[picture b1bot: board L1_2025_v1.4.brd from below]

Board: 4 copper layers, 64.0 x 150.7 mm, 211 parts (2 on the bottom side), 140 nets.

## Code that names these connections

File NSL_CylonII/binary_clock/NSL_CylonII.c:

#include <avr/io.h> 
#include <avr/eeprom.h> 
#include <avr/interrupt.h>
#include <avr/pgmspace.h>

#include <util/delay.h>

#include <stdlib.h>

#define shortdelay(); 			asm("nop\n\tnop\n\t");

#define TIMER1_PRESCALE_1 		(1)
#define TIMER1_PRESCALE_8 		(2)
#define TIMER1_PRESCALE_64 		(3)
#define TIMER1_PRESCALE_256		(4)
#define TIMER1_PRESCALE_1024	(5)

#define MIN_OF(x,y) ((x) < (y) ? (x) : (y))
#define MAX_OF(x,y) ((x) > (y) ? (x) : (y))

#define GET_BIT(a,n)    ((a >> n) & 1)
#define SET_BIT(a,n)    (a|=(1<<n))
#define CLR_BIT(a,n)    (a&=~(1<<n))
#define SWITCH_BIT(a,n) (a^=(1<<n))
#define IS_BIT_SET(a,n) (a & (1<<n))
#define IS_BIT_CLR(a,n) (~(a & (1<<n)))

// 		PORTB,DDRB,PINB

#define ddrb(r,c)  charlieplex[ (r*(3*4)) + ((c*3)+1) ]
#define pinb(r,c)  charlieplex[ (r*(3*4)) + ((c*3)+2) ]
#define portb(r,c) charlieplex[ (r*(3*4)) + ((c*3)+0) ]

#define HEX__(n) 0x##n##LU

/* 8-bit conversion function */
#define B8__(x) ((x&0x0000000FLU)?1:0)	\
	+((x&0x000000F0LU)?2:0)		\
	+((x&0x00000F00LU)?4:0)		\
	+((x&0x0000F000LU)?8:0)		\
	+((x&0x000F0000LU)?16:0)	\
	+((x&0x00F00000LU)?32:0)	\
	+((x&0x0F000000LU)?64:0)	\
	+((x&0xF0000000LU)?128:0)

/* *** user macros ***/

/* for upto 8-bit binary constants */
#define B8(d) ((unsigned char)B8__(HEX__(d)))

/* for upto 16-bit binary constants, MSB first */
#define B16(dmsb,dlsb) (((unsigned short)B8(dmsb)<<	+ B8(dlsb)))

/* for upto 32-bit binary constants, MSB first */
#define B32(dmsb,db2,db3,dlsb) (((unsigned long)B8(dmsb)<<24)	 \
	+ ((unsigned long)B8(db2)<<16) \
	+ ((unsigned long)B8(db3)<<	 \
	+ B8(dlsb))



//  state definitions for each individual LED
// A5  A2  A1  A0  A4  A3
// PD6 PB0 PB1 PB2 PB3 PB4  

// 00 = LOW
// 01 = HIGH
// 11 = X (input)

static const unsigned char PROGMEM led30[] = {

	B8( 1111) , B8(11110100 ),		// LED2
	B8( 1111),  B8(11110001 ),		// LED1
	B8( 1111) , B8(11011100 ),		// LED4
	B8( 1111) , B8(11001101 ),		// LED3
	B8( 1111) , B8(01111100 ),		// LED6
	B8( 1111) , B8(00111101 ),		// LED5
	
	B8( 1111) , B8(11010011 ),		// LED12
	B8( 1111) , B8(11000111 ),		// LED11
	B8( 1111) , B8(01110011 ),		// LED14
	B8( 1111) , B8(00110111 ),		// LED13
	B8( 1101) , B8(11110011 ),		// LED16
	B8( 1100) , B8(11110111 ),		// LED15
	
	B8( 1111) , B8(01001111 ),		// LED20
	B8( 1111) , B8(00011111 ),		// LED19
	B8( 1101) , B8(11001111 ),		// LED22
	B8( 1100),  B8(11011111 ),		// LED21
	B8( 0111) , B8(11001111 ),		// LED24
	B8( 0011) , B8(11011111 ),		// LED23

	B8( 1101) , B8(00111111 ),		// LED26
	B8( 1100) , B8(01111111 ),		// LED25
	B8( 0111) , B8(00111111 ),		// LED28
	B8( 0011) , B8(01111111 ),		// LED27
	B8( 1101) , B8(11111100 ),		// LED8
	B8( 1100),  B8(11111101 ),		// LED7

	B8( 0100) , B8(11111111 ),		// LED30
	B8( 0001) , B8(11111111 ),		// LED29
	B8( 0111) , B8(11110011 ),		// LED18
	B8( 0011) , B8(11110111 ),		// LED17
	B8( 0111) , B8(11111100 ),		// LED10
	B8( 0011) , B8(11111101 ),		// LED9
};


unsigned int X = 0;
signed char XDIR =1;

// this routine is written to help understand how the process works, not fast.
void SetRC( unsigned char R,unsigned char C ) 
{	
	unsigned char b1,b2;
	unsigned char portb, ddrb;

	// get current values, Can't cache PORTD/DDRD since the sound interrupt can change, should cache DDRD6/PORTD6 instead
	portb = PORTB;
	ddrb = DDRB;

	//	read two values from array, we use pgm_read_byte because the data is in program memory space
	// its 6*2 because there are 6 leds in each column, and two bytes per led
	b1 = pgm_read_byte(&led30[ (R*(6*2))+(C*2)   ] ) ;
	b2 = pgm_read_byte(&led30[((R*(6*2))+(C*2))+1] ) ;

	// if  bit positions 32 in b1 == 11 then set to don't care (input ) tristate for PD6
	if( IS_BIT_SET( b1,3 ) && IS_BIT_SET( b1,2 ) ) {

		CLR_BIT(DDRD,6 );

	} else { 

		// otherwise it is set to an output
		SET_BIT(DDRD ,6 );
	}

	// if 10 == 11 then set to don't care (input ) tristate for PB0
	if( GET_BIT( b1,1 )==1 && GET_BIT( b1,0 )==1 ) {

		CLR_BIT(ddrb,0 );

	} else { 

		// otherwise its an output
		SET_BIT(ddrb ,0 );
	}

	// if 76 == 11 then set to don't care (input ) tristate  for PB1
	if( GET_BIT( b2,7 )==1 && GET_BIT( b2,6 )==1 ) {

		CLR_BIT(ddrb,1 );

	} else { 

		// otherwise its an output
		SET_BIT(ddrb ,1 );
	}

	// if 54 == 11 then set to don't care (input ) tristate for PB2
	if( GET_BIT( b2,5 )==1 && GET_BIT( b2,4 )==1 ) {

		CLR_BIT(ddrb,2 );

	} else { 

		// otherwise its an output
		SET_BIT(ddrb ,2 );
	}

	// if 32 == 11 then set to don't care (input ) tristate for PB3
	if( GET_BIT( b2,3 )==1 && GET_BIT( b2,2 )==1 ) {

		CLR_BIT(ddrb,3 );

	} else { 

		// otherwise its an output
		SET_BIT(ddrb ,3 );
	}

	// if 10 == 11 then set to don't care (input ) tristate for PB4
	if( GET_BIT( b2,1 )==1 && GET_BIT( b2,0 )==1 ) {

		CLR_BIT(ddrb,4 );

	} else { 

		// otherwise its an output
		SET_BIT(ddrb ,4 );
	}

	/// all of the DDR's are set

	// if 32 == 00 then set to low for PD6
	if( GET_BIT( b1,3 )==0 && GET_BIT( b1,2 )==0 ) {

		CLR_BIT(PORTD,6 ); //set to off

	// if 32 == 01 then set to high for PD6
	} else if( GET_BIT( b1,3 )==0 && GET_BIT( b1,2 )== 1) { 

		// set to on
		SET_BIT(PORTD ,6 );
	}

	// if 10 == 00 then set to low for PB0
	if( GET_BIT( b1,1 )==0 && GET_BIT( b1,0 )==0 ) {

		CLR_BIT(portb,0); //set to off

	// if 32 == 01 then set to high for PB0
	} else if( GET_BIT( b1,1 )==0 && GET_BIT( b1,0 )==1 ) { 

		// set to on
		SET_BIT(portb ,0 );
	}

	// if 76 == 00 then set to low for PB1
	if( GET_BIT( b2,7 )==0 && GET_BIT( b2,6 )==0 ) {

		CLR_BIT(portb,1); //set to off

	// if 32 == 01 then set to high for PB1
	} else if( GET_BIT( b2,7 )==0 && GET_BIT( b2,6 ) ==1 ) { 

		// set to on
		SET_BIT(portb ,1 );
	}


	// if 54 == 00 then set to low for PB2
	if( GET_BIT( b2,5 )==0 && GET_BIT( b2,4 )==0 ) {

		CLR_BIT(portb,2); //set to off

	// if 32 == 01 then set to high for PB2
	} else if( GET_BIT( b2,5 )==0 && GET_BIT( b2,4 )==1 ) { 

		// set to on
		SET_BIT(portb ,2 );
	}

	// if 32 == 00 then set to low for PB3
	if( GET_BIT( b2,3 )==0 && GET_BIT( b2,2 )==0 ) {

		CLR_BIT(portb,3); //set to off

	// if 32 == 01 then set to high for PB3
	} else if( GET_BIT( b2,3 ) ==0 && GET_BIT( b2,2 )==1 ) { 

		// set to on
		SET_BIT(portb ,3 );
	}

	// if 10 == 00 then set to low for PB4
	if( GET_BIT( b2,1 )==0 && GET_BIT( b2,0 )==0 ) {

		CLR_BIT(portb,4); //set to off

	// if 32 == 01 then set to high for PB4
	} else if( GET_BIT( b2,1)==0 && GET_BIT( b2,0 )==1 ) { 

		// set to on
		SET_BIT(portb ,4 );
	}

	//set all at once.
	PORTB = portb;
	DDRB = ddrb;
}


unsigned char binarytime[] =
{ 
	//6x5
	0x00,	// Hours  - First Digit
	0x00,	// Hours  - Second Digit
	0x00,	// Minutes - First Digit
	0x00,	// Minutes - Second Digit
	0x00	// Seconds
};

// Increments Seconds every second
SIGNAL( SIG_TIMER1_COMPA ) 
{
	binarytime[4]++;

	if(binarytime[4] > 59)	// Increment second digit of minute every minute
	{
		binarytime[4] = 0;	// Reset seconds
		binarytime[3]++;	// Increment second digit of minute
	}
	if(binarytime[3] > 9)
	{
		binarytime[3] = 0;	// Reset second digit of minute
		binarytime[2]++;	// Increment first digit of minute
	}
	if(binarytime[2] > 5)	
	{	
		binarytime[2] = 0;	// Reset first digit of minute
		binarytime[1]++;	// Increment second digit of hour
	}
	if(binarytime[0] == 1)
	{
		if(binarytime[1] > 2)
		{
			binarytime[0] = 0;	// Clear all time, 12-hours have passed
			binarytime[1] = 0;
			binarytime[2] = 0;
			binarytime[3] = 0;
			binarytime[4] = 0;	
		}	
	}
	else
	{
		if(binarytime[1] > 9)
		{
			binarytime[1] = 0;	// Reset second digit of hour
			binarytime[0]++;	// Increment first digit of hour
		}		
	}
	
}


int main(void)
{
	unsigned int R,C;

	// setup timer
	TCCR1B = (1 << WGM12) | TIMER1_PRESCALE_64;
	OCR1A = (uint16_t)1000000;
	TIMSK |= 1 << OCIE1A;   // Output Compare Interrupt Enable (timer 1, OCR1A) 

	//  speaker off (eats power otherwise)
	DDRD = 0xff;
	PIND = 0x0;
	PORTD = 0x10; 
	DDRB = 0;

	// switch on interrupts ( start speaker )
	sei();


	// Display the time
	for(;;) 
	{	
		for ( R= 0 ; R < 5 ; R ++ ) 
		{
			for ( C= 0 ; C < 6 ; C ++ ) 
			{
				if((binarytime[R] >> C) & 0x01)	// Read bit of the Row
				{
					SetRC(R,C); 		
				}
			}
		}
		/*
		if((~PINB & 0x01) >> 0)
		{
			binarytime[3]++;	// Increment second digit of minute
		}
		if((~PINB & 0x01) >> 1)
		{
			binarytime[1]++;	// Increment second digit of hour
		}
		*/
	}
}
